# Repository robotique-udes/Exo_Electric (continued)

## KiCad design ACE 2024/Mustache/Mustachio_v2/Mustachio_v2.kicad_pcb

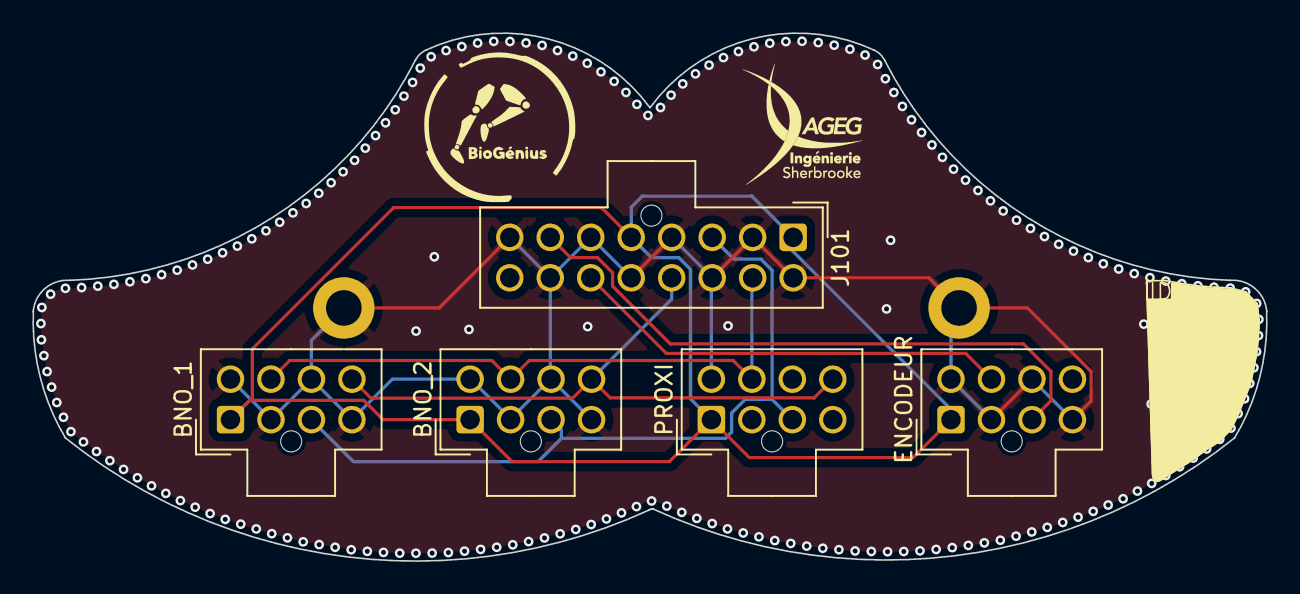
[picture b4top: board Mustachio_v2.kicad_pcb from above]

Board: 2 copper layers, 76.2 x 32.6 mm, 7 parts (0 on the bottom side), 7 nets.

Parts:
BNO_1, BNO_2: Conn_I2C; Molex_Nano-Fit_105310-xx08_2x04_P2.50mm_Vertical
ENCODEUR: Conn_Encodeur; Molex_Nano-Fit_105310-xx08_2x04_P2.50mm_Vertical
H101, H102: MountingHole_Pad; MountingHole_2.2mm_M2_ISO14580_Pad
J101: Conn_I2C+Enc; Molex_Nano-Fit_105310-xx16_2x08_P2.50mm_Vertical
PROXI: Conn_Capt_Distance; Molex_Nano-Fit_105310-xx08_2x04_P2.50mm_Vertical

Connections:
ENC_IntA: ENCODEUR.3, J101.7
ENC_IntB: ENCODEUR.6, J101.14
GND: BNO_1.2, BNO_1.4, BNO_1.5, BNO_1.7, BNO_2.2, BNO_2.4, BNO_2.5, BNO_2.7, ENCODEUR.2, ENCODEUR.4, ENCODEUR.5, ENCODEUR.7, H101.1, H102.1, J101.2, J101.4, J101.6, J101.8, J101.9, J101.11, J101.13, J101.15, PROXI.5
RESET: BNO_1.8, BNO_2.8, J101.12, PROXI.8
SCL_I2C: BNO_1.3, BNO_2.3, J101.3, PROXI.3
SDA_I2C: BNO_1.6, BNO_2.6, J101.10, PROXI.6
Vcc_3v3: BNO_1.1, BNO_2.1, ENCODEUR.1, J101.1, J101.5, PROXI.1

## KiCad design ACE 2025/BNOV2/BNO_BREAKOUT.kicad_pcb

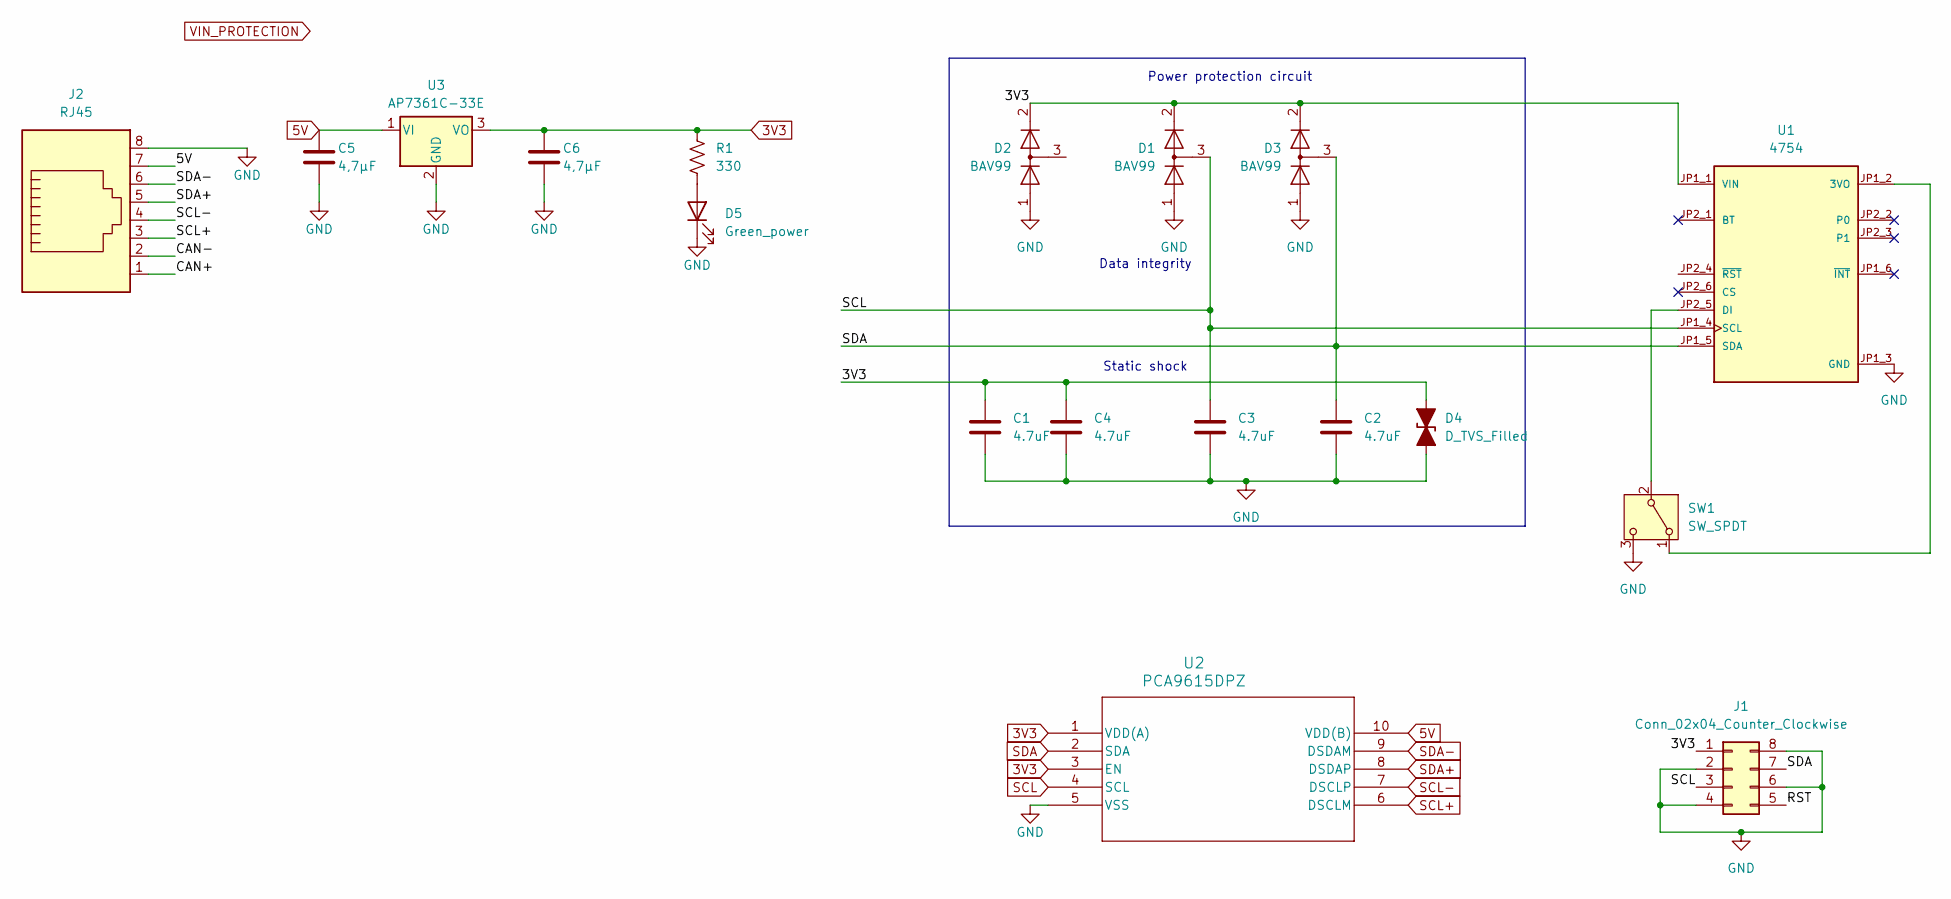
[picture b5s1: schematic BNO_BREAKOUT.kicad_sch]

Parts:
C1, C2, C3, C4: 4.7uF; C_1812_4532Metric_Pad1.57x3.40mm_HandSolder
C5, C6: 4,7µF; C_0805_2012Metric_Pad1.18x1.45mm_HandSolder
D1, D2, D3: BAV99; SOT-23
D4: D_TVS_Filled
D5: Green_power; D_0805_2012Metric
J1: Conn_02x04_Counter_Clockwise; Molex_Nano-Fit_105314-xx08_2x04_P2.50mm_Horizontal
J2: RJ45; RJ45_Amphenol_54602-x08_Horizontal
R1: 330; R_0805_2012Metric_Pad1.20x1.40mm_HandSolder
SW1: SW_SPDT; SW_SPDT_CK_JS102011SAQN
U1: 4754; MODULE_4754; PARTREV 2021-03-16
U2: PCA9615DPZ; TSSOP10_SOT552-1_NXP
U3: AP7361C-33E; SOT-223-3_TabPin2

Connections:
3V3: C1.1, C4.1, C6.2, D1.2 (A), D2.2 (A), D3.2 (A), D4.2 (A2), J1.1, R1.1, U1.JP1_1 (VIN), U2.1 (VDD(A)), U2.3 (EN), U3.3 (VO)
5V: C5.2, J2.7, U2.10 (VDD(B)), U3.1 (VI)
/CAN+: J2.1
/CAN-: J2.2
GND: C1.2, C2.2, C3.2, C4.2, C5.1, C6.1, D1.1 (K), D2.1 (K), D3.1 (K), D4.1 (A1), D5.1 (K), J1.2, J1.4, J1.6, J1.8, J2.8, SW1.3 (C), U1.JP1_3 (GND), U2.5 (VSS), U3.2 (GND)
unnamed: D5.2 (A), R1.2
unnamed: SW1.1 (A), U1.JP1_2 (3VO)
unnamed: SW1.2 (B), U1.JP2_5 (DI)
SCL: C3.1, D1.3 (K), J1.3, U1.JP1_4 (SCL), U2.4 (SCL)
SCL+: J2.3, U2.6 (DSCLM)
SCL-: J2.4, U2.7 (DSCLP)
SDA: C2.1, D3.3 (K), J1.7, U1.JP1_5 (SDA), U2.2 (SDA)
SDA+: J2.5, U2.8 (DSDAP)
SDA-: J2.6, U2.9 (DSDAM)

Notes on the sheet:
Power protection circuit
Data integrity
Static shock

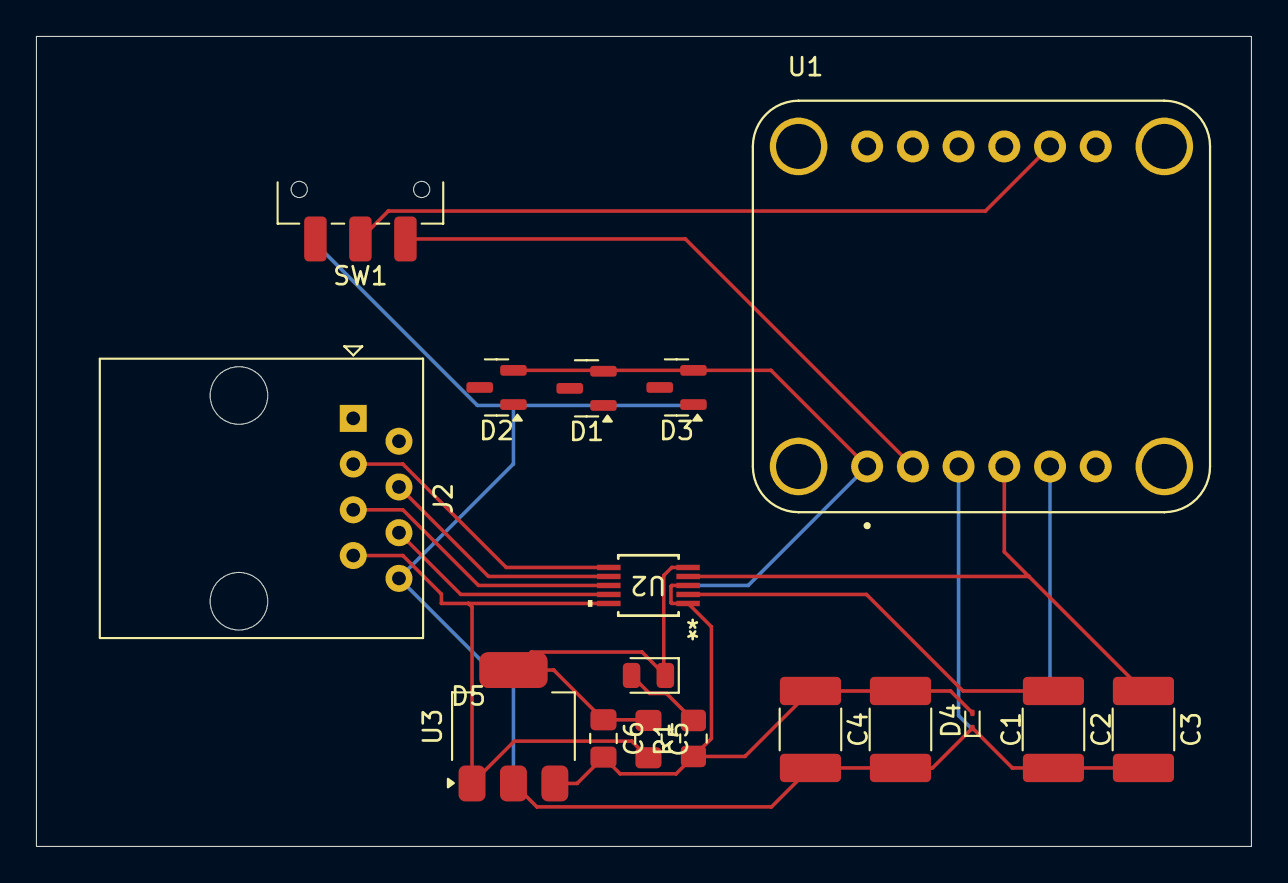
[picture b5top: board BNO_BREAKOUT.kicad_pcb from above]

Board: 2 copper layers, 67.5 x 45.0 mm, 17 parts (0 on the bottom side), 12 nets.

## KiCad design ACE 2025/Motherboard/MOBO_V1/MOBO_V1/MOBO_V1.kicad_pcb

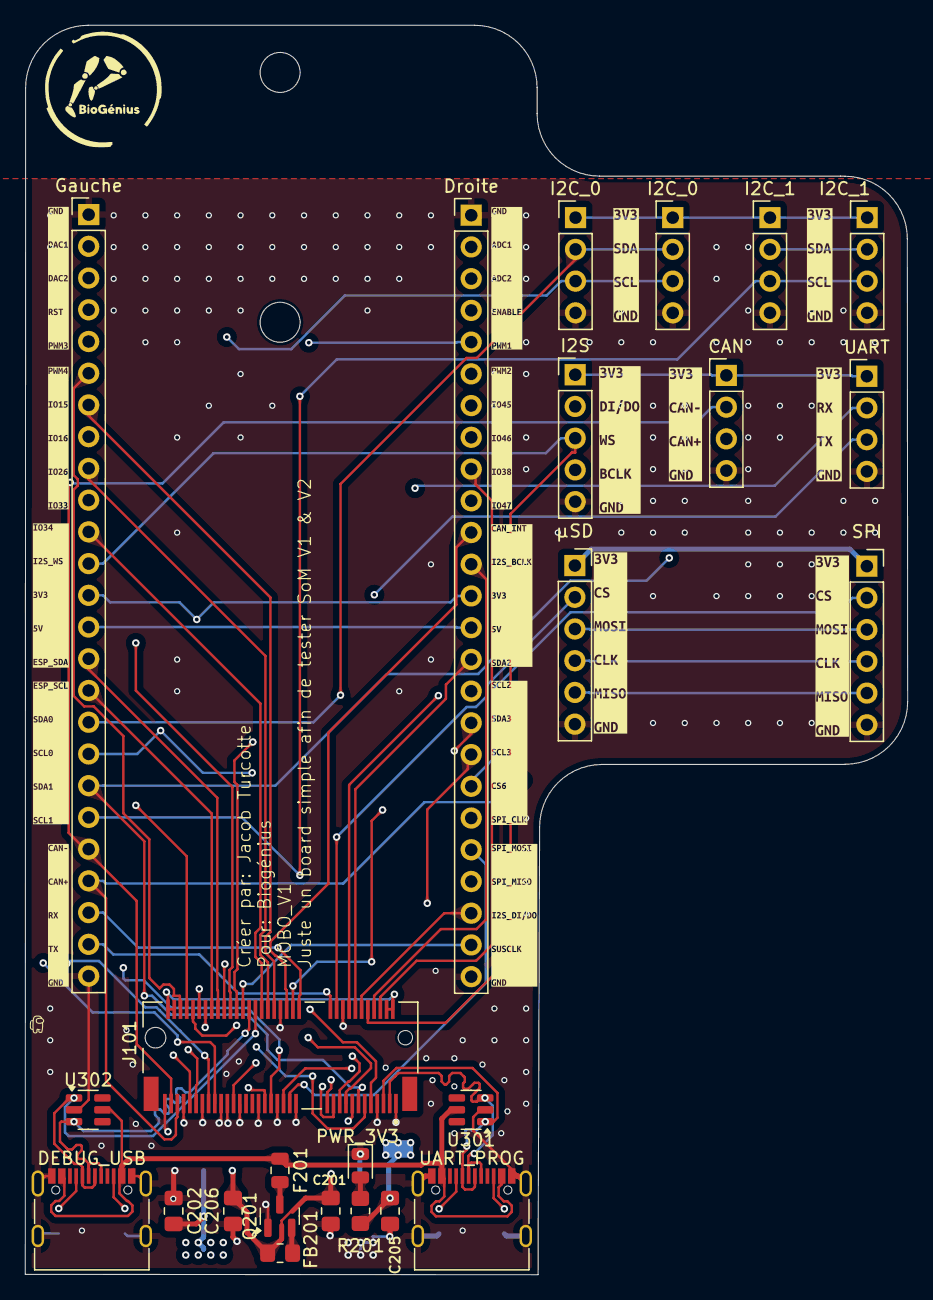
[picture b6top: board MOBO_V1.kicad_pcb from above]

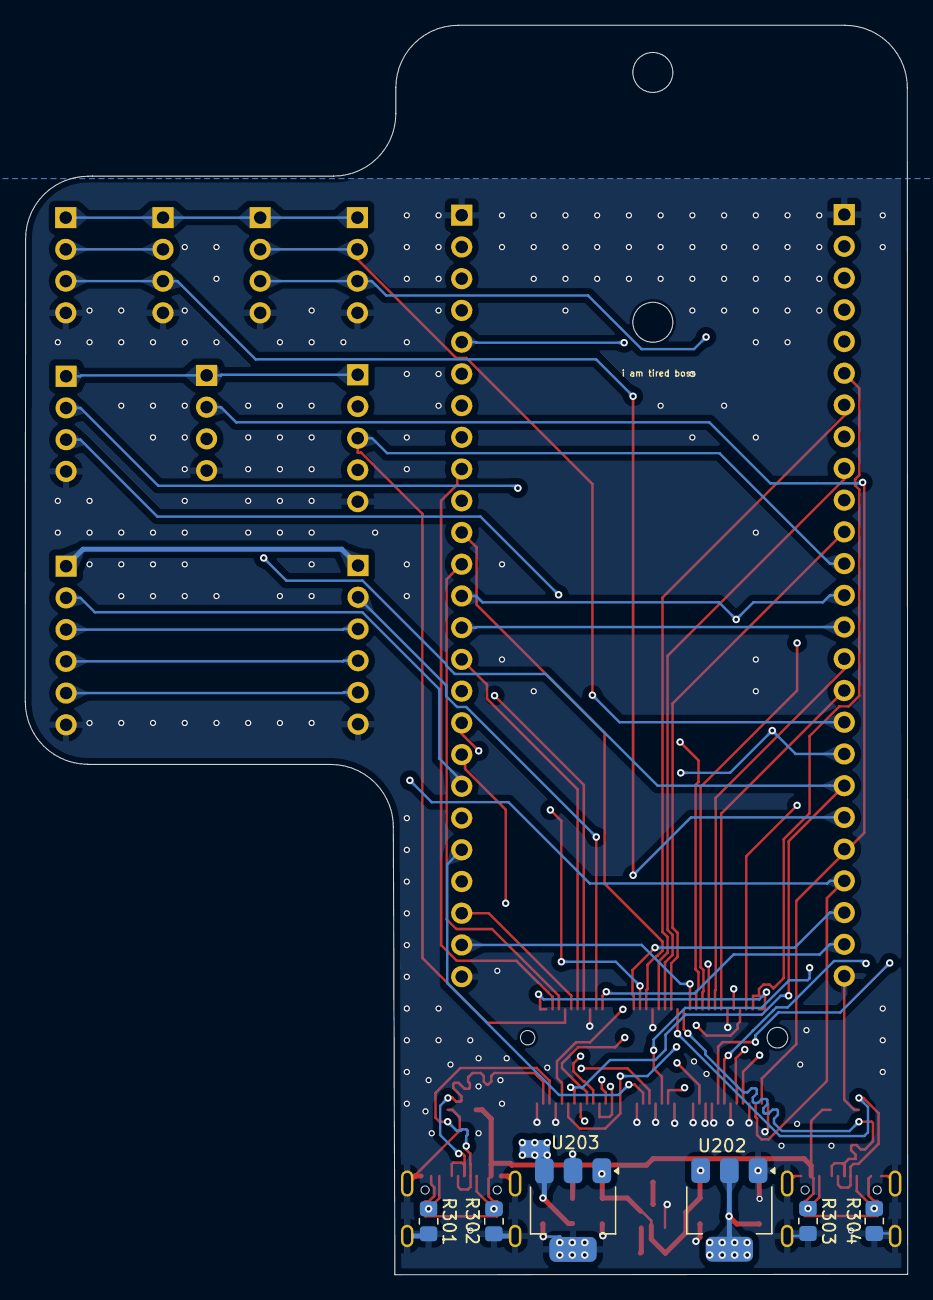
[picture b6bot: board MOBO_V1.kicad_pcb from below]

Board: 4 copper layers, 70.6 x 100.0 mm, 50 parts (6 on the bottom side), 60 nets.

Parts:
C201: 10uF; C_0805_2012Metric_Pad1.18x1.45mm_HandSolder
C202: 22µF; C_0805_2012Metric_Pad1.18x1.45mm_HandSolder
C205, C206: 4,7µF; C_0805_2012Metric_Pad1.18x1.45mm_HandSolder
CAN: CAN_BUS; PinHeader_1x04_P2.54mm_Vertical
DEBUG_USB: USB_C_DEBUG; USB_C_Receptacle_G-Switch_GT-USB-7010ASV
Droite: Droite; PinHeader_1x25_P2.54mm_Vertical
F201: SMD0805B110TF; Fuse_0805_2012Metric
FB201: 600 @ 100MHz; R_0805_2012Metric_Pad1.20x1.40mm_HandSolder
Gauche: Gauche; PinHeader_1x25_P2.54mm_Vertical
I2C_0: I2C_0_1; PinHeader_1x04_P2.54mm_Vertical
I2C_0#2: I2C_0_0; PinHeader_1x04_P2.54mm_Vertical
I2C_1: I2C_1_0; PinHeader_1x04_P2.54mm_Vertical
I2C_1#2: I2C_1_1; PinHeader_1x04_P2.54mm_Vertical
I2S: I2S; PinHeader_1x05_P2.54mm_Vertical
J101: AMPHENOL_MDT320E01001
PWR_3V3: Green_power; D_0805_2012Metric
Q201: AO3401A; SOT-23
R201: 330; R_0805_2012Metric_Pad1.20x1.40mm_HandSolder
R301, R302, R303, R304: 5.1k; R_0805_2012Metric_Pad1.20x1.40mm_HandSolder
SPI: Conn_SPI; PinSocket_1x06_P2.54mm_Vertical
U202: AMS1117-5.0; SOT-223-3_TabPin2
U203: AP7361C-33E; SOT-223-3_TabPin2
U301, U302: SRV05-4; SOT-23-6
UART: UART; PinHeader_1x04_P2.54mm_Vertical
UART_PROG: USB_C_UART; USB_C_Receptacle_G-Switch_GT-USB-7010ASV
V1_mount, V2_mount: MountingHole_3.2mm_M3
kibuzzard-66C7DEE4, kibuzzard-66C7DEE4#2: G***; kibuzzard-66C7DEE4
kibuzzard-66C7DFF5: G***; kibuzzard-66C7DFF5
kibuzzard-66C7E0B6, kibuzzard-66C7E0B6#2: G***; kibuzzard-66C7E0B6
kibuzzard-66C7E03B: G***; kibuzzard-66C7E03B
kibuzzard-66C7E5D1: G***; kibuzzard-66C7E5D1
kibuzzard-66C7E5F8: G***; kibuzzard-66C7E5F8
kibuzzard-66C7E7D8: G***; kibuzzard-66C7E7D8
kibuzzard-66C7E69C: G***; kibuzzard-66C7E69C
kibuzzard-66C7E73E: G***; kibuzzard-66C7E73E
kibuzzard-66C7E79D: G***; kibuzzard-66C7E79D
kibuzzard-66C7E81E: G***; kibuzzard-66C7E81E
kibuzzard-66C7E082: G***; kibuzzard-66C7E082
kibuzzard-66C7E82F: G***; kibuzzard-66C7E82F
kibuzzard-66C7E605: G***; kibuzzard-66C7E605
kibuzzard-66C7E879: G***; kibuzzard-66C7E879
µSD: Conn_Module_SD; PinSocket_1x06_P2.54mm_Vertical

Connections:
+3.3V: SPI.1, µSD.1
ADC_1: Droite.2, J101.65 (ADC_1_MCP3202)
ADC_2: Droite.3, J101.67 (ADC_2_MCP3202)
CAN_H: CAN.3, Gauche.22, J101.71 (CAN_H_MCP2515)
CAN_L: CAN.2, Gauche.21, J101.73 (CAN_L_MCP2515)
CHIP_EN: Droite.4, J101.56 (RESET_ESP32)
DAC_1: Gauche.2, J101.59 (DAC_1_MCP48)
DAC_2: Gauche.3, J101.61 (DAC_2_MCP48)
DEBUG_D+: DEBUG_USB.A6 (D+), DEBUG_USB.B6 (D+), J101.48 (USB_DEBUG_D+), U302.3 (IO2)
DEBUG_D-: DEBUG_USB.A7 (D-), DEBUG_USB.B7 (D-), J101.46 (USB_DEBUG_D-), U302.1 (IO1)
FT231_D+: J101.3 (USB_D+_FT231), U301.3 (IO2), UART_PROG.A6 (D+), UART_PROG.B6 (D+)
FT231_D-: J101.5 (USB_D-_FT231), U301.1 (IO1), UART_PROG.A7 (D-), UART_PROG.B7 (D-)
GND: C201.1, C202.1, C205.1, C206.1, CAN.4, DEBUG_USB.A1 (GND), DEBUG_USB.A12 (GND), DEBUG_USB.B1 (GND), DEBUG_USB.B12 (GND), DEBUG_USB.S1 (SHIELD), Droite.1, Droite.25, Gauche.1, Gauche.25, I2C_0.4, I2C_0#2.4, I2C_1.4, I2C_1#2.4, I2S.5, J101.1 (GND), J101.7 (GND), J101.18 (GND), J101.33 (GND), J101.38 (GND), J101.39 (GND), J101.45 (GND), J101.51 (GND), J101.55 (GND), J101.57 (GND), J101.62 (GND), J101.63 (GND), J101.69 (GND), J101.75 (GND), PWR_3V3.1 (K), Q201.1 (G), R301.2, R302.2, R303.2, R304.2, SPI.6, U202.1 (GND), U203.2 (GND), U301.2 (VN), U302.2 (VN), UART.4, UART_PROG.A1 (GND), UART_PROG.A12 (GND), UART_PROG.B1 (GND), UART_PROG.B12 (GND), UART_PROG.S1 (SHIELD), µSD.6
GPIO15: Gauche.7, J101.40 (GPIO15)
GPIO16: Gauche.8, J101.41 (GPIO16)
GPIO17_U1_TXD: Gauche.24, J101.22 (UART_TX), UART.3
GPIO18_U1_RXD: Gauche.23, J101.32 (UART_RX), UART.2
GPIO26: Gauche.9, J101.42 (GPIO26)
GPIO33: Gauche.10, J101.43 (GPIO33)
GPIO34: Gauche.11, J101.44 (GPIO34)
GPIO38_ADDRESSABLE_LED: Droite.9, J101.6 (GPIO38&LED)
GPIO45: Droite.7, J101.52 (GPIO45)
GPIO46: Droite.8, J101.53 (GPIO46)
GPIO47: Droite.10, J101.34 (GPIO47)
GPIO48/CAN_INT: Droite.11, J101.36 (GPIO48)
I2C_SCL_0_TCA: Gauche.18, I2C_0.3, I2C_0#2.3, J101.11 (I2C_SCL_1_TCA)
I2C_SCL_1_TCA: Gauche.20, I2C_1.3, I2C_1#2.3, J101.15 (I2C_SCL_2_TCA)
I2C_SCL_2_TCA: Droite.16, J101.16 (I2C_SCL_3_TCA)
I2C_SCL_3_TCA: Droite.18, J101.19 (I2C_SCL_4_TCA)
I2C_SCL_ESP32: Gauche.16, J101.60 (I2C_SCL_ESP32)
I2C_SDA_0_TCA: Gauche.17, I2C_0.2, I2C_0#2.2, J101.9 (I2C_SDA_1_TCA)
I2C_SDA_1_TCA: Gauche.19, I2C_1.2, I2C_1#2.2, J101.13 (I2C_SDA_2_TCA)
I2C_SDA_2_TCA: Droite.15, J101.14 (I2C_SDA_3_TCA)
I2C_SDA_3_TCA: Droite.17, J101.17 (I2C_SDA_4_TCA)
I2C_SDA_ESP32: Gauche.15, J101.58 (I2C_SDA_ESP32)
I2S_BCLK: Droite.12, I2S.4, J101.8 (I2S_BCLK)
I2S_DIN/DOUT: Droite.23, I2S.2, J101.12 (I2S_DIN/DOUT)
I2S_WS: Gauche.12, I2S.3, J101.10 (I2S_WS)
unnamed: PWR_3V3.2 (A), R201.2
unnamed: R302.1, UART_PROG.A5 (CC1)
unnamed: R301.1, UART_PROG.B5 (CC2)
unnamed: DEBUG_USB.A5 (CC1), R304.1
unnamed: DEBUG_USB.B5 (CC2), R303.1
unnamed: F201.2, Q201.3 (D)
unnamed: FB201.1, Q201.2 (S)
PWM_1: Droite.5, J101.64 (PWM_1_PCA)
PWM_2: Droite.6, J101.66 (PWM_2_PCA)
PWM_3: Gauche.5, J101.68 (PWM_3_PCA)
PWM_4: Gauche.6, J101.70 (PWM_4_PCA)
RESET_OTHERS: Gauche.4, J101.54 (RESET_AUTRES)
SPI_5_ESP32: J101.20 (SPI_CS_5), µSD.2
SPI_6_ESP32: Droite.19, J101.21 (SPI_CS_6), SPI.2
SPI_CLK_ESP32: Droite.20, J101.23 (SPI_CLK), SPI.4, µSD.4
SPI_MISO_ESP32: Droite.22, J101.37 (SPI_MISO), SPI.5, µSD.5
SPI_MOSI_ESP32: Droite.21, J101.35 (SPI_MOSI), SPI.3, µSD.3
SUSCLK: Droite.24, J101.50 (SUSCLK)
VBUS: DEBUG_USB.A4 (VBUS), DEBUG_USB.A9 (VBUS), DEBUG_USB.B4 (VBUS), DEBUG_USB.B9 (VBUS), F201.1, U301.5 (VP), U302.5 (VP), UART_PROG.A4 (VBUS), UART_PROG.A9 (VBUS), UART_PROG.B4 (VBUS), UART_PROG.B9 (VBUS)
VIN_PROTECTION: C201.2, C206.2, FB201.2, U202.3 (VI), U203.1 (VI)
Vcc_3V3: C205.2, CAN.1, Droite.13, Gauche.13, I2C_0.1, I2C_0#2.1, I2C_1.1, I2C_1#2.1, I2S.1, J101.2 (Vcc_3v3), J101.4 (Vcc_3v3), J101.72 (Vcc_3v3), J101.74 (Vcc_3v3), R201.1, U203.3 (VO), UART.1
Vcc_5V: C202.2, Droite.14, Gauche.14, U202.2 (VO)

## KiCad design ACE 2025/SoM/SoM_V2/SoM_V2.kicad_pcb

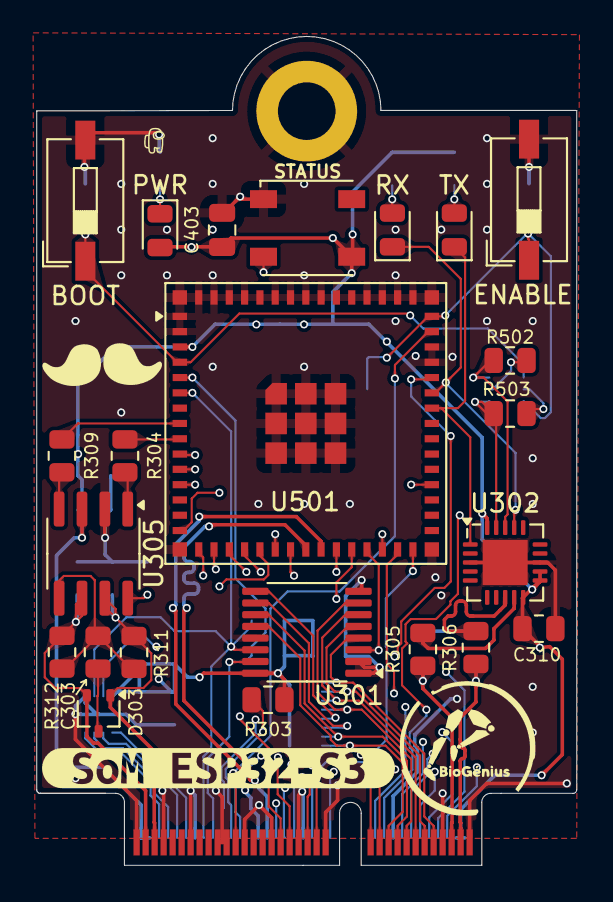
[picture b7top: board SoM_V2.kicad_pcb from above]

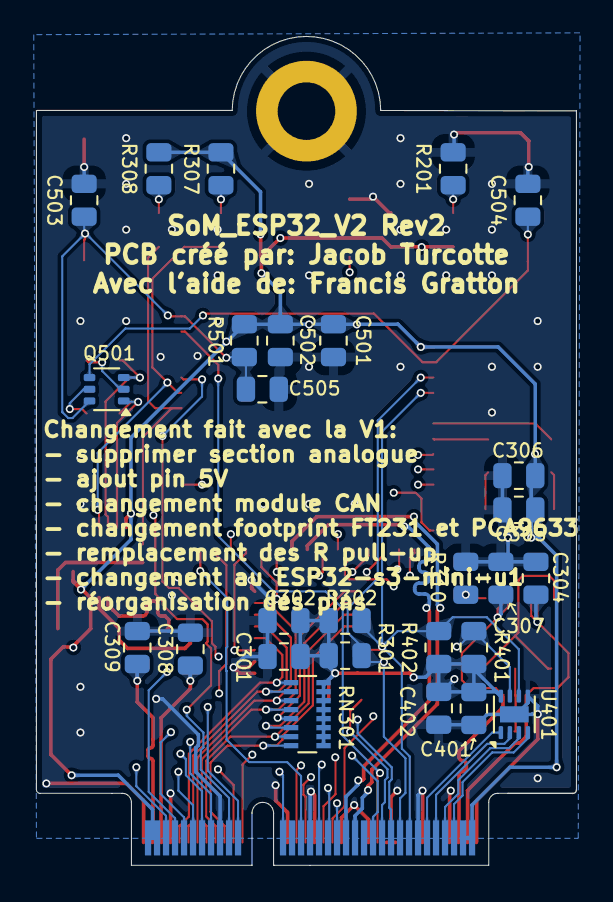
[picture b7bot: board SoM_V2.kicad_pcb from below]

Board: 4 copper layers, 30.0 x 46.1 mm, 52 parts (27 on the bottom side), 62 nets.

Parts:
BOOT: SW_BOOT; SW_DIP_SPSTx01_Slide_6.7x4.1mm_W6.73mm_P2.54mm_LowProfile_J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
C301, C501: 10µF; R_0805_2012Metric
C302, C304, C306, C307, C310, C502, C504, C505: 0.1µF; R_0805_2012Metric
C303, C305, C401, C503: 1µF; R_0805_2012Metric
C308, C309: 47pF; R_0805_2012Metric
C402: 100nF; R_0805_2012Metric
C403: 100n; C_0805_2012Metric
D303: SP0502BAJT; SOT-323_SC-70
ENABLE: SW_CHIP_EN; SW_DIP_SPSTx01_Slide_6.7x4.1mm_W6.73mm_P2.54mm_LowProfile_J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
PWR: GREEN; LED_0805_2012Metric
Q501: MBT3904DW1T1G; SOT-363_SC-70-6
R201, R307, R308: 330; R_0805_2012Metric
R301, R302, R303, R304, R309, R310, R401, R402: 1k; R_0805_2012Metric
R305, R306: 27; R_0805_2012Metric
R311, R312: 60; R_0805_2012Metric
R501, R502, R503: 10k; R_0805_2012Metric
RN301: R_Pack08_Split; R_Array_Convex_8x0602
RX: TX; LED_0805_2012Metric
STATUS: FZ2812-5050; LED_Inolux_IN-PI554FCH_PLCC4_5.0x5.0mm_P3.2mm
TX: RX; LED_0805_2012Metric
U201: NGFF_E
U301: TCA9546APWR; TSSOP-16_4.4x5mm_P0.65mm
U302: FT231XQ; QFN-20-1EP_4x4mm_P0.5mm_EP2.5x2.5mm
U305: SN65HVD230; SOIC-8_3.9x4.9mm_P1.27mm
U401: PCA9633DP1; DFN-8-1EP_2x2mm_P0.5mm_EP0.9x1.6mm
U501: ESP32-S3-MINI-1U; ESP32-S2-MINI-1U
kibuzzard-66E094ED: G***; kibuzzard-66E094ED

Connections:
/Communication/CAN+: C307.2, D303.1 (K), R311.1, U201.71 (CAN_H_MCP2515), U305.7 (CANH)
/Communication/CAN-: C304.1, D303.2 (K), R312.2, U201.73 (CAN_L_MCP2515), U305.6 (CANL)
/Communication/D+: R306.2, U302.8 (USBDP)
/Communication/D-: R305.2, U302.9 (USBDM)
/Communication/DR+: C309.1, R306.1, U201.3 (USB_D+_FT231)
/Communication/DR-: C308.1, R305.1, U201.5 (USB_D-_FT231)
CHIP_EN: C503.1, C505.1, ENABLE.1, Q501.6 (C1), R501.2, U201.56 (RESET_ESP32), U501.45 (EN)
CS_1: U201.20 (CS_1), U501.15 (IO11)
CS_2: U201.21 (CS_2), U501.25 (IO21)
DEBUG+: U201.48 (USB_DEBUG_D+), U501.24 (IO20)
DEBUG-: U201.46 (USB_DEBUG_D-), U501.23 (IO19)
DTR: Q501.3 (C2), R502.1, U302.18 (~DTR)
GND: BOOT.2, C301.2, C302.2, C304.2, C305.2, C306.2, C307.1, C308.2, C309.2, C310.2, C401.2, C402.2, C403.2, C501.2, C502.2, C503.2, C504.2, C505.2, ENABLE.2, R201.2, R310.1, STATUS.1 (VSS), U201.1 (GND), U201.7 (GND), U201.18 (GND), U201.33 (GND), U201.38 (GND), U201.39 (GND), U201.45 (GND), U201.51 (GND), U201.55 (GND), U201.57 (GND), U201.62 (GND), U201.63 (GND), U201.69 (GND), U201.75 (GND), U301.1 (A0), U301.2 (A1), U301.8 (GND), U301.13 (A2), U302.3 (GND), U302.13 (GND), U302.21 (GND), U305.2 (GND), U401.5 (GND), U501.1 (GND), U501.2 (GND), U501.42 (GND), U501.43 (GND), U501.46 (GND), U501.47 (GND), U501.48 (GND), U501.49 (GND), U501.50 (GND), U501.51 (GND), U501.52 (GND), U501.53 (GND), U501.54 (GND), U501.55 (GND), U501.56 (GND), U501.57 (GND), U501.58 (GND), U501.59 (GND), U501.60 (GND), U501.61 (GND), U501.62 (GND), U501.63 (GND), U501.64 (GND), U501.65 (GND)
GPIO0_BOOT: BOOT.1, C504.1, Q501.4 (E2), U501.4 (IO0)
GPIO4/RXD: R309.1, U501.8 (IO4)
GPIO5/TXD: R304.1, U501.9 (IO5)
GPIO15: U201.40 (GPIO15), U501.19 (IO15)
GPIO16: U201.41 (GPIO16), U501.20 (IO16)
GPIO17_U1_TXD: U201.22 (UART_TX), U501.21 (IO17)
GPIO18_U1_RXD: U201.32 (UART_RX), U501.22 (IO18)
GPIO26: U201.42 (GPIO26), U501.26 (IO26)
GPIO33: U201.43 (GPIO33), U501.28 (IO33)
GPIO34: U201.44 (GPIO34), U501.29 (IO34)
GPIO38_ADDRESSABLE_LED: STATUS.2 (DIN), U201.6 (GPIO38&LED), U501.34 (IO38)
GPIO45: U201.52 (GPIO45), U501.41 (IO45)
GPIO46: U201.53 (GPIO46), U501.44 (IO46)
GPIO48/CAN_INT: U201.36 (GPIO48), U501.30 (IO48)
I2C_SCL_0_TCA: RN301.2 (R2.1), U201.11 (I2C_SCL_1_TCA), U301.5 (SC0)
I2C_SCL_1_TCA: RN301.4 (R4.1), U201.15 (I2C_SCL_2_TCA), U301.7 (SC1)
I2C_SCL_2_TCA: RN301.6 (R6.1), U201.16 (I2C_SCL_3_TCA), U301.10 (SC2)
I2C_SCL_3_TCA: RN301.8 (R8.1), U201.19 (I2C_SCL_4_TCA), U301.12 (SC3)
I2C_SCL_ESP32: R302.2, R402.2, U201.60 (I2C_SCL_ESP32), U301.14 (SCL), U401.6 (SCL6), U501.6 (IO2)
I2C_SDA_0_TCA: RN301.1 (R1.1), U201.9 (I2C_SDA_1_TCA), U301.4 (SD0)
I2C_SDA_1_TCA: RN301.3 (R3.1), U201.13 (I2C_SDA_2_TCA), U301.6 (SD1)
I2C_SDA_2_TCA: RN301.5 (R5.1), U201.14 (I2C_SDA_3_TCA), U301.9 (SD2)
I2C_SDA_3_TCA: RN301.7 (R7.1), U201.17 (I2C_SDA_4_TCA), U301.11 (SD3)
I2C_SDA_ESP32: R301.2, R401.2, U201.58 (I2C_SDA_ESP32), U301.15 (SDA), U401.7 (SDA), U501.5 (IO1)
I2S_BCLK: U201.8 (I2S_BCLK), U501.16 (IO12)
I2S_DIN/DOUT: U201.12 (I2S_DIN/DOUT), U501.18 (IO14)
I2S_WS: U201.10 (I2S_WS), U501.17 (IO13)
unnamed: PWR.2 (A), R201.1
unnamed: R307.1, RX.2 (A)
unnamed: R308.1, TX.2 (A)
unnamed: C303.2, D303.3 (A)
unnamed: Q501.2 (B1), R502.2
unnamed: Q501.5 (B2), R503.2
unnamed: U201.64 (PWM_1_PCA), U401.1 (PWM1)
unnamed: U201.66 (PWM_2_PCA), U401.2 (PWM2)
unnamed: U201.68 (PWM_3_PCA), U401.3 (PWM3)
unnamed: U201.70 (PWM_4_PCA), U401.4 (PWM4)
unnamed: R304.2, U305.1 (D)
unnamed: R309.2, U305.4 (R)
unnamed: R310.2, U305.8 (Rs)
RESET_OTHERS: R303.2, U201.54 (RESET_AUTRES), U301.3 (RESET_N), U501.27 (IO47)
RTS: Q501.1 (E1), R503.1, U302.19 (~RTS)
SPI_CLK_ESP32: U201.23 (SPI_CLK), U501.10 (IO6)
SPI_MISO_ESP32: U201.37 (SPI_MISO), U501.12 (IO8)
SPI_MOSI_ESP32: U201.35 (SPI_MOSI), U501.11 (IO7)
U0RXD: RX.1 (K), U302.17 (TXD), U501.40 (RXD0)
U0TXD: TX.1 (K), U302.1 (RXD), U501.39 (TXD0)
Vcc_3V3: C301.1, C302.1, C305.1, C306.1, C310.1, C401.1, C402.1, C403.1, C501.1, C502.1, PWR.1 (K), R301.1, R302.1, R303.1, R307.2, R308.2, R401.1, R402.1, R501.1, RN301.9 (R8.2), RN301.10 (R7.2), RN301.11 (R6.2), RN301.12 (R5.2), RN301.13 (R4.2), RN301.14 (R3.2), RN301.15 (R2.2), RN301.16 (R1.2), STATUS.3 (VDD), U201.2 (Vcc_3v3), U201.4 (Vcc_3v3), U201.72 (Vcc_3v3), U201.74 (Vcc_3v3), U301.16 (VCC), U302.10 (3V3OUT), U302.11 (~RESET), U302.12 (VCC), U302.20 (VCCIO), U305.3 (VCC), U401.8 (VCC), U501.3 (3V3)
Vref_CAN: C303.1, R311.2, R312.1, U305.5 (Vref)

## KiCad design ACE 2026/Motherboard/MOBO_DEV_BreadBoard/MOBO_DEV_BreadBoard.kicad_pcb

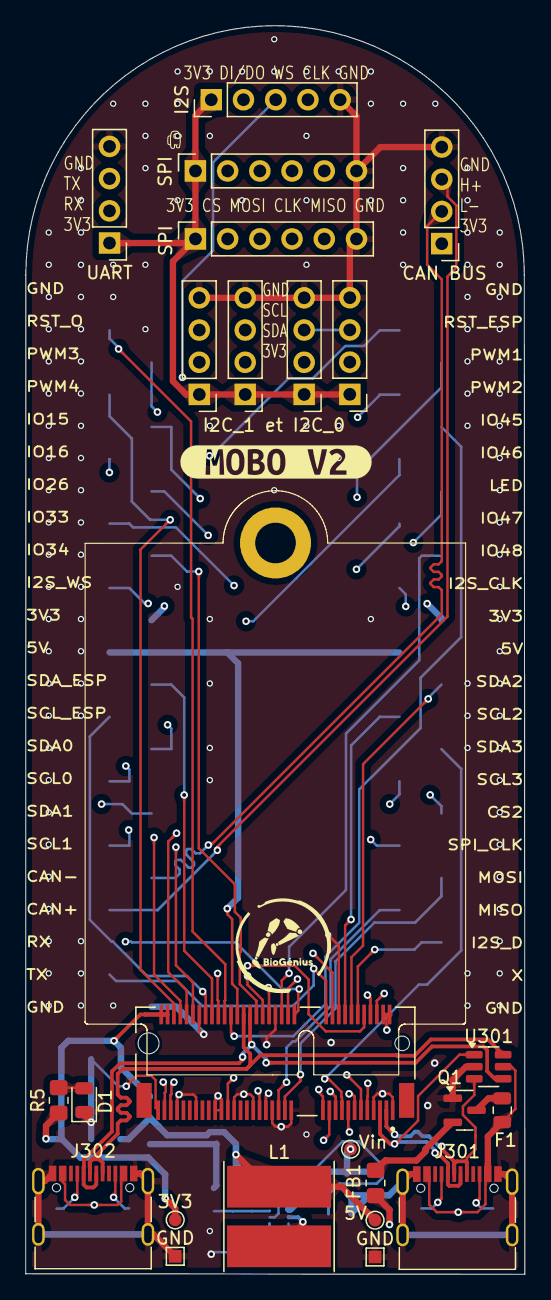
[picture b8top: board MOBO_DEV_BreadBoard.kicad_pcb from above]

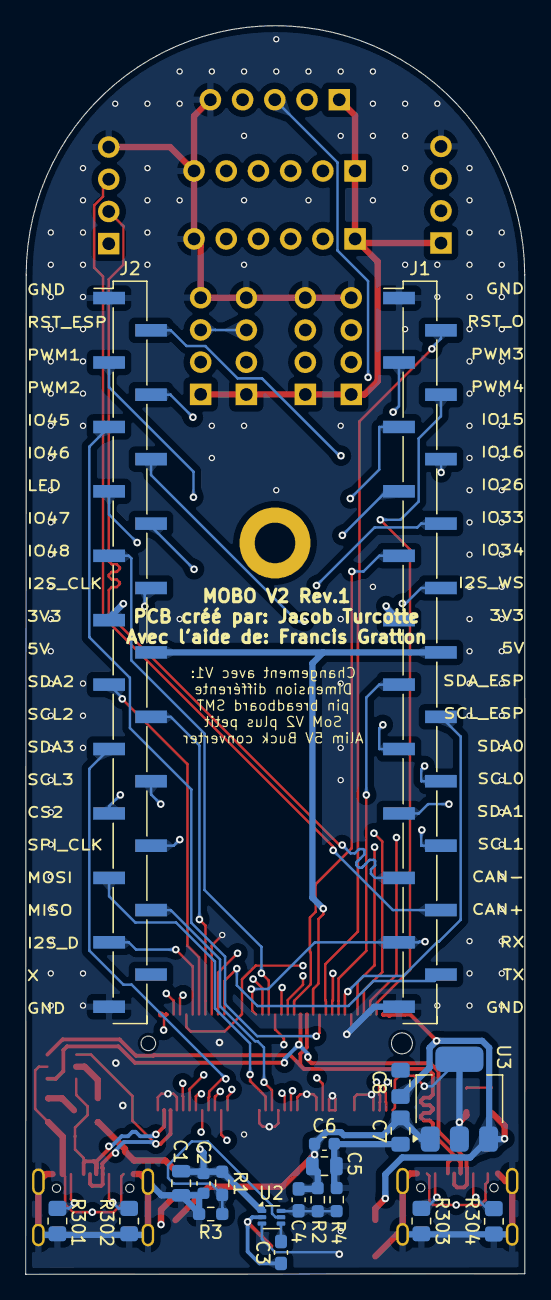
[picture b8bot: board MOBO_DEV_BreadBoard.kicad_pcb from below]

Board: 4 copper layers, 39.4 x 98.5 mm, 45 parts (20 on the bottom side), 58 nets.

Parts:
3V3: TP_3v3; TestPoint_Pad_D1.0mm
5V: TP_5V; TestPoint_Pad_D1.0mm
C1: 10µF; C_0805_2012Metric
C2, C6: 0,1µF; C_0603_1608Metric
C3: 0,1µF; C_0603_1608Metric_Pad1.08x0.95mm_HandSolder
C4: 33pF; C_0603_1608Metric_Pad1.08x0.95mm_HandSolder
C5: 22µF; C_0805_2012Metric
C7, C8: 4,7µF; C_0805_2012Metric_Pad1.18x1.45mm_HandSolder
CAN BUS: CAN_BUS; PinHeader_1x04_P2.54mm_Vertical
D1: Green_power; D_0805_2012Metric
F1: SMD0805B110TF; Fuse_0805_2012Metric
FB1: 600 @ 100MHz; R_0805_2012Metric_Pad1.20x1.40mm_HandSolder
GND: TP_GND; TestPoint_Pad_1.0x1.0mm
GND#2: TP_GND_IN; TestPoint_Pad_1.0x1.0mm
I2S: I2S; PinHeader_1x05_P2.54mm_Vertical
J1: Gauche; PinHeader_1x23_P2.54mm_Vertical_SMD_Pin1Left
J2: Droite; PinHeader_1x23_P2.54mm_Vertical_SMD_Pin1Left
J301: USB_C_UART; USB_C_Receptacle_G-Switch_GT-USB-7010ASV
J302: USB_C_DEBUG; USB_C_Receptacle_G-Switch_GT-USB-7010ASV
J307: I2C_0_0; PinHeader_1x04_P2.54mm_Vertical
J308: I2C_0_1; PinHeader_1x04_P2.54mm_Vertical
J309: I2C_1_0; PinHeader_1x04_P2.54mm_Vertical
J310: I2C_1_1; PinHeader_1x04_P2.54mm_Vertical
L1: 3,3µH 20mOhm; L_TDK_VLP8040
Q1: AO3401A; SOT-23
R1: 100k; R_0603_1608Metric_Pad0.98x0.95mm_HandSolder
R2: 158k; R_0603_1608Metric_Pad0.98x0.95mm_HandSolder
R3: 28k; R_0603_1608Metric_Pad0.98x0.95mm_HandSolder
R4: 30k; R_0603_1608Metric_Pad0.98x0.95mm_HandSolder
R5: 330; R_0805_2012Metric_Pad1.20x1.40mm_HandSolder
R301, R302, R303, R304: 5.1k; R_0805_2012Metric_Pad1.20x1.40mm_HandSolder
SPI: Conn_SPI; PinSocket_1x06_P2.54mm_Vertical
SPI#2: Conn_Module_SD; PinSocket_1x06_P2.54mm_Vertical
U1: AMPHENOL_MDT320E01001
U2: TPS562242DRLR; SOT-563
U3: AP7361C-33E; SOT-223-3_TabPin2
U301: SRV05-4; SOT-23-6
UART: UART; PinHeader_1x04_P2.54mm_Vertical
Vin: TP_VIN; TestPoint_Pad_D1.0mm
kibuzzard-66E82988: G***; kibuzzard-66E82988

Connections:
CAN_N: CAN BUS.2, J1.19, U1.73 (CAN_L_MCP2515)
CAN_P: CAN BUS.3, J1.20, U1.71 (CAN_H_MCP2515)
CHIP_EN: J2.2, U1.56 (RESET_ESP32)
CS_1: SPI#2.2, U1.20 (CS_1)
CS_2: J2.17, SPI.2, U1.21 (CS_2)
DEBUG_D+: J302.A6 (D+), J302.B6 (D+), U1.48 (USB_DEBUG_D+), U301.6 (IO4)
DEBUG_D-: J302.A7 (D-), J302.B7 (D-), U1.46 (USB_DEBUG_D-), U301.4 (IO3)
FT231_D+: J301.A6 (D+), J301.B6 (D+), U1.3 (USB_D+_FT231), U301.3 (IO2)
FT231_D-: J301.A7 (D-), J301.B7 (D-), U1.5 (USB_D-_FT231), U301.1 (IO1)
GND: C1.2, C2.2, C5.2, C6.2, C7.1, C8.1, CAN BUS.4, D1.1 (K), GND.1, GND#2.1, I2S.5, J1.1, J1.23, J2.1, J2.23, J301.A1 (GND), J301.A12 (GND), J301.B1 (GND), J301.B12 (GND), J301.S1 (SHIELD), J302.A1 (GND), J302.A12 (GND), J302.B1 (GND), J302.B12 (GND), J302.S1 (SHIELD), J307.4, J308.4, J309.4, J310.4, Q1.1 (G), R3.2, R4.2, R301.2, R302.2, R303.2, R304.2, SPI.6, SPI#2.6, U1.1 (GND), U1.7 (GND), U1.18 (GND), U1.33 (GND), U1.38 (GND), U1.39 (GND), U1.45 (GND), U1.51 (GND), U1.55 (GND), U1.57 (GND), U1.62 (GND), U1.63 (GND), U1.69 (GND), U1.75 (GND), U2.3 (GND), U3.2 (GND), U301.2 (VN), UART.4
GPIO15: J1.5, U1.40 (GPIO15)
GPIO16: J1.6, U1.41 (GPIO16)
GPIO17_U1_TXD: J1.22, U1.22 (UART_TX), UART.3
GPIO18_U1_RXD: J1.21, U1.32 (UART_RX), UART.2
GPIO26: J1.7, U1.42 (GPIO26)
GPIO33: J1.8, U1.43 (GPIO33)
GPIO34: J1.9, U1.44 (GPIO34)
GPIO38_ADDRESSABLE_LED: J2.7, U1.6 (GPIO38&LED)
GPIO45: J2.5, U1.52 (GPIO45)
GPIO46: J2.6, U1.53 (GPIO46)
GPIO47: J2.8, U1.34 (RST_OTHER)
GPIO48/CAN_INT: J2.9, U1.36 (GPIO48)
I2C_SCL_0_TCA: J1.16, J307.3, J308.3, U1.11 (I2C_SCL_1_TCA)
I2C_SCL_1_TCA: J1.18, J309.3, J310.3, U1.15 (I2C_SCL_2_TCA)
I2C_SCL_2_TCA: J2.14, U1.16 (I2C_SCL_3_TCA)
I2C_SCL_3_TCA: J2.16, U1.19 (I2C_SCL_4_TCA)
I2C_SCL_ESP32: J1.14, U1.60 (I2C_SCL_ESP32)
I2C_SDA_0_TCA: J1.15, J307.2, J308.2, U1.9 (I2C_SDA_1_TCA)
I2C_SDA_1_TCA: J1.17, J309.2, J310.2, U1.13 (I2C_SDA_2_TCA)
I2C_SDA_2_TCA: J2.13, U1.14 (I2C_SDA_3_TCA)
I2C_SDA_3_TCA: J2.15, U1.17 (I2C_SDA_4_TCA)
I2C_SDA_ESP32: J1.13, U1.58 (I2C_SDA_ESP32)
I2S_BCLK: I2S.4, J2.10, U1.8 (I2S_BCLK)
I2S_DIN/DOUT: I2S.2, J2.21, U1.12 (I2S_DIN/DOUT)
I2S_WS: I2S.3, J1.10, U1.10 (I2S_WS)
unnamed: D1.2 (A), R5.2
unnamed: J301.A5 (CC1), R302.1
unnamed: J301.B5 (CC2), R301.1
unnamed: J302.A5 (CC1), R304.1
unnamed: J302.B5 (CC2), R303.1
unnamed: F1.2, Q1.3 (D)
unnamed: FB1.1, Q1.2 (S)
unnamed: R1.2, R3.1, U2.5 (EN)
unnamed: C3.1, L1.1, U2.2 (SW)
unnamed: C3.2, U2.4 (VBST)
unnamed: C4.2, R2.2, R4.1, U2.6 (VFB)
PWM_1: J2.3, U1.64 (PWM_1_PCA)
PWM_2: J2.4, U1.66 (PWM_2_PCA)
PWM_3: J1.3, U1.68 (PWM_3_PCA)
PWM_4: J1.4, U1.70 (PWM_4_PCA)
RESET_OTHERS: J1.2, U1.54 (RESET_AUTRES)
SPI_CLK_ESP32: J2.18, SPI.4, SPI#2.4, U1.23 (SPI_CLK)
SPI_MISO_ESP32: J2.20, SPI.5, SPI#2.5, U1.37 (SPI_MISO)
SPI_MOSI_ESP32: J2.19, SPI.3, SPI#2.3, U1.35 (SPI_MOSI)
VBUS: F1.1, J301.A4 (VBUS), J301.A9 (VBUS), J301.B4 (VBUS), J301.B9 (VBUS), J302.A4 (VBUS), J302.A9 (VBUS), J302.B4 (VBUS), J302.B9 (VBUS), U301.5 (VP)
VIN_PROTECTION: C1.1, C2.1, FB1.2, R1.1, U2.1 (VIN), Vin.1
Vcc_3V3: 3V3.1, C8.2, CAN BUS.1, I2S.1, J1.11, J2.11, J307.1, J308.1, J309.1, J310.1, R5.1, SPI.1, SPI#2.1, U1.2 (Vcc_3v3), U1.4 (Vcc_3v3), U1.72 (Vcc_3v3), U1.74 (Vcc_3v3), U3.3 (VO), UART.1
Vcc_5V: 5V.1, C4.1, C5.1, C6.1, C7.2, J1.12, J2.12, L1.2, R2.1, U1.50 (Vcc_5V), U3.1 (VI)
